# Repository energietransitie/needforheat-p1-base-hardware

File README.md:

# NeedForHeat P1-BASE hardware <!-- omit in toc -->

This repository contains the open hardware design files for the NeedForHeat P1-BASE device, which can be used as a [CoreInk BASE extension module](https://docs.m5stack.com/en/coreink/proto_base), on the back of an [M5Stack CoreInk](https://docs.m5stack.com/en/core/coreink) device. 

The NeedForHeat P1-BASE enables reading [smart meters that adhere to the Dutch Smart Meter Requirements](https://github.com/energietransitie/dsmr-info) via the [P1 port](https://nl.wikipedia.org/wiki/P1-poort).

## Table of contents <!-- omit in toc -->
- [General info](#general-info)
- [Producing](#producing)
  - [Printed Circuit Board](#printed-circuit-board)
  - [Enclosure](#enclosure)
- [Deploying](#deploying)
  - [Cost](#cost)
  - [Connecting](#connecting)
  - [Setting the DIP Switches](#setting-the-dip-switches)
- [Developing](#developing)
  - [Printed Circuit Board](#printed-circuit-board-1)
- [Features](#features)
- [Status](#status)
- [License](#license)
- [Credits](#credits)

## General info
This repository contains the open hardware designs files for the NeedForHeat P1-BASE. It also includes a `docs` folder with recent printouts of the [schematics](./docs/needforheat-p1-base-hardware-sch.pdf) and [PCB layout](./docs/needforheat-p1-base-hardware-pcb.pdf). 

For the associated firmware that you can run on this device, please see [this repository](https://github.com/energietransitie/needforheat-p1-reader-firmware).

## Producing

### Printed Circuit Board
To manufacture the printed circuit board you can use various PCB services. 

The folder [pcb/jlcpcb](./pcb/jlcpcb) includes all exported files needed to have the PCBs manufactured by [JLCPCB](https://www.jlcpcb.com). Upload the [zipped gerber files](./pcb/jlcpcb/assembly/GERBER-needforheat-p1-base-hardware.zip) to the [JLCPCB quote page](https://cart.jlcpcb.com/quote), select the amount of PCBs and a colour for the silkscreen. All other options can be left on default. 

If you do not want to solder components on the PCB yourself, select `PCB assembly` and JLCPCB will do it for you (even for through-hole components if you so desire). This will take you to a page where the BOM and POS file can be uploaded. Use the files [BOM-needforheat-p1-base-hardware.csv](./pcb/jlcpcb/assembly/BOM-needforheat-p1-base-hardware.csv) and [CPL-needforheat-p1-base-hardware.csv](./pcb/jlcpcb/assembly/CPL-needforheat-p1-base-hardware.csv).

JLCPCB provides detailed steps on their website to select component assembly, including wave soldering. For wave soldering or through-hole component assembly, specify this requirement when uploading your BOM and POS files. 

> After uploading BOM and CPL, you may be asked to select a component for `Q3`. You do not need to do so and can select 'do not place'. For more information, see the [design document](docs/documentation.md#optional-components).

### Enclosure

An enclosure for this device has not been developed yet.

<!-- an enclosure has not been developed yet
To fabricate the enclosure you can use your own 3D printer or use a 3D printing service. 

The folder [enclosure/fabrication](./enclosure/fabrication) contains exported STL files for the [case](./enclosure/fabrication/twomes-hardware-repository-template-case.stl) and [lid](./enclosure/twomes-hardware-repository-template-lid.step) of the NeedForHeat P1-BASE enclosure. The STL files can be imported into any slicer and turned into G-Code for a 3D printer.
-->

## Deploying

To deploy P1-BASE to a home as the NeedForHeat Smart Meter module, in addition to the PCB you need additional hardware: enclusure, M5Stack CoreInk, a short RJ12 cable and for some homes a power adapter. In this section we describe the cose and connections.

### Cost

Prices indicate price per module in June 2024, based on ordering enough hardware for 10 modules, including 21% VAT and shipping to an address in the Netherlands.

| #   | Item                                                                                                                                                 | Supplier    | Price per Unit |   Subtotal |  Shipping |      Total |
| --- | ---------------------------------------------------------------------------------------------------------------------------------------------------- | ----------- | -------------: | ---------: | --------: | ---------: |
| 1   | P1-BASE PCB                                                                                                                                          | JLCPCB      |          €2.40 |      €2.40 |     €2.38 |      €4.78 |
| 1   | P1-BASE enclosure                                                                                                                                    | JLCPCB      |          €1,30 |      €1,30 |     €2,40 |      €3,60 |
| 1   | [M5Stack CoreInk](https://www.tinytronics.nl/nl/platformen-en-systemen/m5stack/e-paper/m5stack-m5core-ink-met-1.54-inch-e-paper-e-ink-display-esp32) | TinyTronics |         €43.00 |     €43.00 |     €0.00 |     €43.00 |
| 4   | [LEGO pen stroef + pen stroef](https://www.blokjeskoning.nl/product/pen-stroef-pen-stroef-zwart/) | Blokjeskoning |         €0.03 |   €0.12 |    €0.30 | €0.42 |
| 1   | [RJ12 cable (male-male; 6P6C; straight; 0.5 m or shorter)](https://www.amazon.nl/-/en/InLine-18848A-Modular-Cable-6-Core/dp/B005I1UDOE/)[^1]         | AlleKabels  |          €5.95 |      €5.95 |     €0.00 |      €5.95 |
| 1   | [USB-A 230V charger + USB-A to USB-C cable](https://www.allekabels.nl/usb-oplader/4508/3636716/usb-a-oplader-usb-c-kabel.html)                       | AlleKabels  |         €14.95 |     €14.95 |     €0.13 |     €15.08 |
|     | **TOTAL**                                                                                                                                            |             |     **€67.60** | **€67.72** | **€6,21** | **€72,83** |

[^1]: The shorter the cable the better: this allows users to simply click in the RJ12 connector of te to the P1 port of their smart to leave and leave the NeedForHeat smart meter reader device dangling from the P1-port;*

### Connecting

Assuming that the PCB is fully assembled, the device has an enclosure, and the device has been programmed with the [needforheat-p1-reader-firmware](https://github.com/energietransitie/needforheat-p1-reader-firmware), you can proceed and connect the device as follows:

Before sending the device to a home:

1. Mount the P1-BASE in its enclosure.
1. Connect the short RJ12 cable to the upper female RJ12 connector[^2].
1. Insert 2 lego pens in the enclusure at opposite diagonal corners. 
1. Insert 2 lego pens in the holes on the back side of the M5Stack CoreInk at opposite diagonal corners.
4. Do NOT connect the P1_BASE and M5Stack CoreInk, before sending, since they will not fit in a standard [PostNL brievenbusdoos](https://shop.postnl.nl/webshop/verpakkingen/brievenbusdoos-a5-255x160x28mm) when stacked.

[^2]: By pre-connecting the RJ12 cable to connector `J2` on the PCB, you help users at home avoid installation errors. You may even consider clipping off 3 to 4 mm from the latch of the modular conector. After insertion the connector does not protrude from the female connecto, which clearly signals to the user that this cable should not be deinstalled. 

After receiving the device in a home:
1. Connect to the P1-BASE to the based of the M5Stack CoreInk, ensuring alignment of M5Stack CoreInk with the P1-BASE; the LEGO pins will help make sure that the 2x8 pin connector of the P1-BASE properly connects to M5Stack CoreInk.
2. Unplug your existing smart meter reader (if any) from the P1 port smart meter
3. Connect the plug of the NeedForHeat smart meter module in the P1 port .
4. Plug the RJ16 connector of our existing smart meter reader into the bottom RJ12 socket of the P1-BASE.

### Setting the DIP Switches

The hardware version v2.7 (2024-06-07) features 3 DIP switches on the PCB to control data request line management. Adjust the switches according to the following settings before delivering the device to the user:

| DIP-switch Number | ON Position                                        | OFF Position                                          |
| ----------------- | -------------------------------------------------- | ----------------------------------------------------- |
| 1                 | Data requested continuously (DSMR 4 & 5)           | Data not requested continuously                       |
| 2                 | Data request driven by M5Stack CoreInk             | Data request from M5Stack CoreInk ignored             |
| 3                 | Data request driven by external smart meter reader | Data request from external smart meter reader ignored |

If multiple DIP switches are ON simultaneously, data is requested if any corresponding source requires it. This may cause the external smart meter reader to receive partial messages, but according to the [DSMR P1 Port Companion Standard](https://github.com/energietransitie/dsmr-info?tab=readme-ov-file#dsmr-versions-standards) since version 3.0, smart meter readers should be able to handle partial messages.

## Developing

### Printed Circuit Board
To change the hardware design of the PCB, you need:
* [KiCad version 8.0.0 or later](https://www.kicad.org/download/) installed to change te PCB design. 

The KiCad source files of the PCB can be found in the folder [pcb](./pcb).

To convert the PCBs into a format suitable for fabrication, consult the webpage of your PCB manufacturer of choice. For example, see the [JLCPCB guide on how to export Gerbers](https://support.jlcpcb.com/article/149-how-to-generate-gerber-and-drill-files-in-kicad) and the  [JLCPCB guide how to export the BOM and POS files](https://support.jlcpcb.com/article/84-how-to-generate-the-bom-and-centroid-file-from-kicad). You may also use a KiCad plug-in for this purpose such as [kicad-jlcpcb-tools](https://github.com/Bouni/kicad-jlcpcb-tools).

<!-- 
### Enclosure
To change the hardware design of the enclosure, you need either:
* [Autodesk Fusion 360](https://www.kicad.org/download/) installed (Autodesk provides 30 day free trials and [free one-year educational access](https://www.autodesk.com/education/edu-software/overview?sorting=featured&filters=individual) to its products and services for eligible students, teachers and research staff); 
* or [FreeCAD](https://www.freecadweb.org/), an open source alternative.

The source files of the enclosure can be found in the folder [enclosure](./enclosure). We include both .f3d source files and .step source files we obtained after conversion.
-->

## Features

The NeedForHeat P1-BASE includes the following main hardware components:

- [x] Built-in P1-splitter for connecting an additional smart meter reader to the lower female RJ12 connector (`J3`).
- [x] Integrated [Schmitt trigger](https://en.wikipedia.org/wiki/Schmitt_trigger) to reduce signal noise.
- [x] 3 DIP-switches on the PCB for enabling/disabling data request line management.
- [x] Bottom-side 2x8 pin header for MI-BUS connection to the [M5Stack CoreInk](https://docs.m5stack.com/en/core/coreink) (requires soldering yourself, or a hefty JLCPCB fee for bottom-side hand-soldering).

To-do:

- [ ] Test compatibility with Landis+Gyr E360 series smart meters (e.g., [Landis+Gyr CD2D](https://www.landisgyr.eu/), [CM3D](https://www.landisgyr.eu/)).
- [ ] Consider using 'upside-down' RJ12 female connectors for easier [M5Stack CoreInk](https://docs.m5stack.com/en/core/coreink) screen readability.
- [ ] Evaluate relocating and optimizing the 2x8 pin header from the bottom side to the top side of the PCB to reduce manufacturing costs. 
  > (This would also obviate the need for 'upside-down' RJ12 female connectors, above.)
- [ ] Refine PCB design to reduce clutter where possible.
- [ ] Experiment with alternative data request management methods (e.g., MOSFETs, BJTs), which would allow the [M5Stack CoreInk](https://docs.m5stack.com/en/core/coreink) to check and control data request management in software.
- [ ] Implement low-power LEDs for indicating power status, data request status, and data flow.
- [ ] Develop energy-efficient charging strategies for the [M5Stack CoreInk](https://docs.m5stack.com/en/core/coreink) 390 mAh LiPo battery from DSMR 4 and DSMR 5 smart meters, without triggering the fold-back current limiting feature of some smart meters.
- [ ] Design a 3D-printable enclosure compatible with the [M5Stack CoreInk](https://docs.m5stack.com/en/core/coreink), potentially using [LEGO connector pens](https://www.blokjeskoning.nl/product/pen-stroef-pen-stroef-zwart/). A preliminary version can be found in the [needforheat-boiler-monitor-hardware repository](https://github.com/energietransitie/needforheat-boiler-monitor-hardware).

## Status
Project is:  _in progress_

## License
The hardware designs in this repository are available under the [CERN-OHL-P v2 license](./LICENSE), Copyright 2024 [Research group Energy Transition, Windesheim University of Applied Sciences](https://windesheim.nl/energietransitie)

## Credits
This open hardware design is a collaborative effort of:
* Rick de Graaf · [@277r](https://github.com/277r) 
* Gerwin ten Have · [@GerwintenHave](https://github.com/GerwintenHave) 

Product owners:
* Henri ter Hofte · [@henriterhofte](https://github.com/henriterhofte) · Twitter [@HeNRGi](https://twitter.com/HeNRGi)
* Marco Winkelman · [@MarcoW71](https://github.com/MarcoW71)

We use and gratefully acknowlegde the efforts of the makers of:
* [Twomes P1 Gateway Hardware](https://github.com/energietransitie/twomes-p1-gateway-hardware), by Research group Energy Transition at Windesheim University of Applied Sciences, licenced under Apache 2.0
* [KiCad Libraries](https://kicad.github.io/), by the KiCad Development Team, licensed under [an adapted version of the CC-BY-SA 4.0 License](https://www.kicad.org/libraries/license/)

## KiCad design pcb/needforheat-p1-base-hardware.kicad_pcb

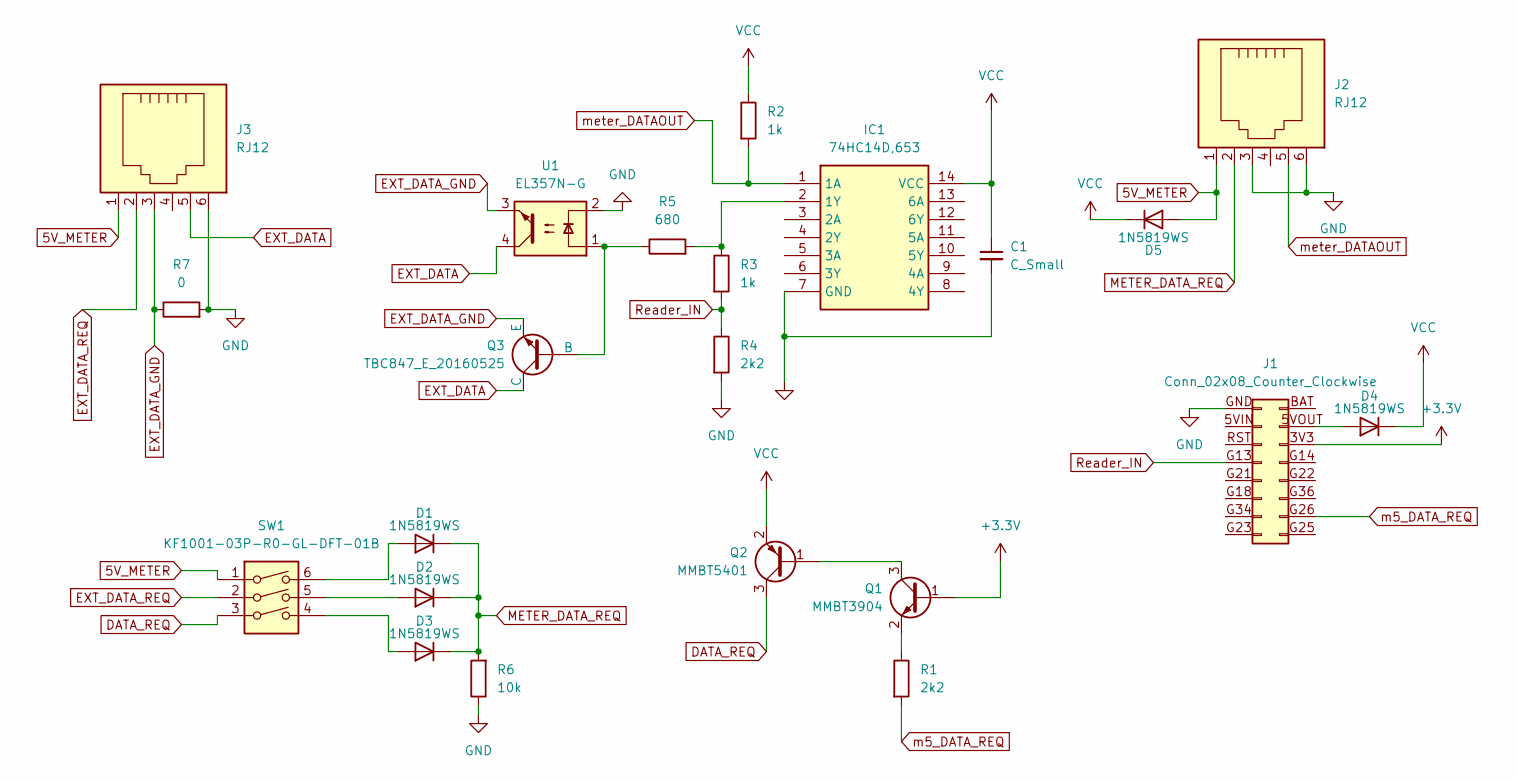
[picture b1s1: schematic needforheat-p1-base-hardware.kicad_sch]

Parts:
C1: C_Small; C_0805_2012Metric
D1, D2, D3, D4, D5: 1N5819WS; D_SOD-323
IC1: 74HC14D,653; SOIC127P600X175-14N; Mouser Part Number 771-74HC14D-T
J1: Conn_02x08_Counter_Clockwise; PinHeader_2x08_P2.54mm_Vertical
J2, J3: RJ12; RJ25_Wayconn_MJEA-660X1_Horizontal
Q1: MMBT3904; SOT-23
Q2: MMBT5401; SOT-23
Q3: TBC847_E_20160525; SOT-23-3
R1, R4: 2k2; R_0805_2012Metric
R2, R3: 1k; R_0805_2012Metric
R5: 680; R_0805_2012Metric
R6: 10k; R_0805_2012Metric
R7: 0; R_0805_2012Metric
SW1: KF1001-03P-R0-GL-DFT-01B; DIP-6_W7.62mm_Socket
U1: EL357N-G; SOP-4_3.8x4.1mm_P2.54mm

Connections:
5V_METER: D5.2 (A), J2.1, J3.1, SW1.1
+3.3V: J1.3V3 (Pin_14), Q1.1 (B)
DATA_REQ: Q2.3 (C), SW1.3
EXT_DATA: J3.5, Q3.1 (C), U1.4
EXT_DATA_GND: J3.3, Q3.3 (E), R7.1, U1.3
EXT_DATA_REQ: J3.2, SW1.2
GND: C1.2, IC1.7 (GND), J1.GND (Pin_1), J2.3, J2.6, J3.6, R4.2, R6.1, R7.2, U1.2
METER_DATA_REQ: D1.1 (K), D2.1 (K), D3.1 (K), J2.2, R6.2
unnamed: D1.2 (A), SW1.6
unnamed: D2.2 (A), SW1.5
unnamed: D3.2 (A), SW1.4
unnamed: D4.2 (A), J1.5VOUT (Pin_15)
unnamed: IC1.2 (1Y), R3.1, R5.2
unnamed: Q1.3 (C), Q2.1 (B)
unnamed: Q1.2 (E), R1.1
unnamed: Q3.2 (B), R5.1, U1.1
Reader_IN: J1.G13 (Pin_4), R3.2, R4.1
VCC: C1.1, D4.1 (K), D5.1 (K), IC1.14 (VCC), Q2.2 (E), R2.1
m5_DATA_REQ: J1.G26 (Pin_10), R1.2
meter_DATAOUT: IC1.1 (1A), J2.5, R2.2

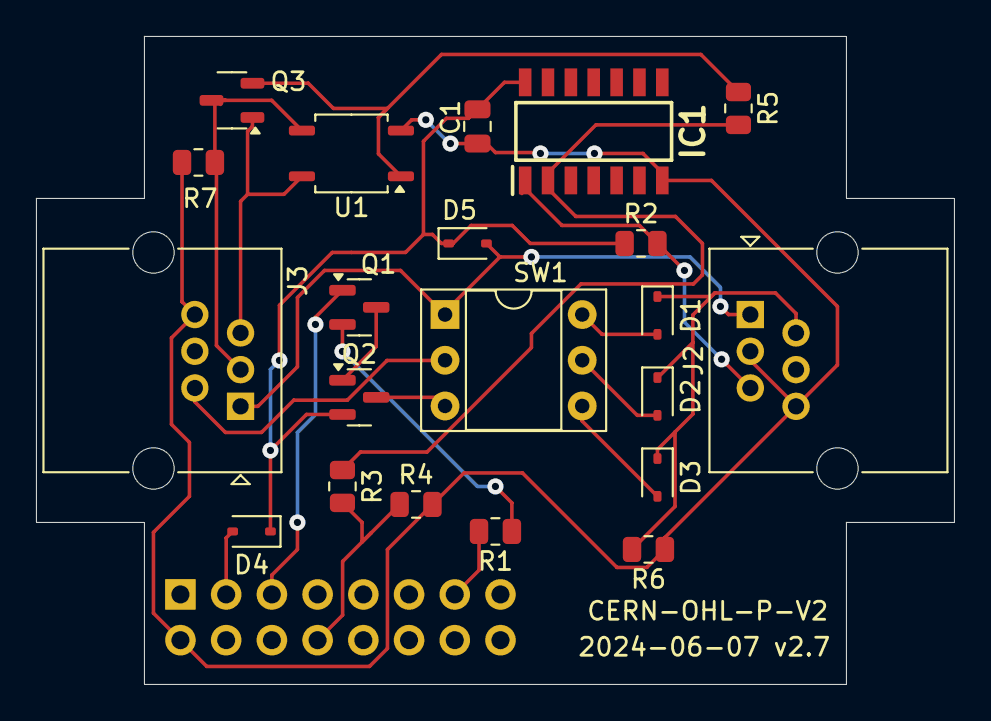
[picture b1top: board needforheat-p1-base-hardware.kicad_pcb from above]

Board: 2 copper layers, 51.0 x 36.0 mm, 22 parts (1 on the bottom side), 20 nets.

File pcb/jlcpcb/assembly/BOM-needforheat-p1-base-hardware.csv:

Comment,Designator,Footprint,LCSC
10k,R6,R_0805_2012Metric,C17414
1k,"R2,R3",R_0805_2012Metric,C17513
2k2,"R1,R4",R_0805_2012Metric,C17520
1N5819WS,"D1,D2,D3,D4,D5",D_SOD-323,C191023
MMBT3904,Q1,SOT-23,C20526
680,R5,R_0805_2012Metric,C23228
EL357N-G,U1,SOP-4_3.8x4.1mm_P2.54mm,C29981
C_Small,C1,C_0805_2012Metric,C49678
"74HC14D,653",IC1,SOIC127P600X175-14N,C5605
Conn_02x08_Counter_Clockwise,J1,PinHeader_2x08_P2.54mm_Vertical,C68234
RJ12,"J2,J3",RJ25_Wayconn_MJEA-660X1_Horizontal,C77859
MMBT5401,Q2,SOT-23,C8326
KF1001-03P-R0-GL-DFT-01B,SW1,DIP-6_W7.62mm_Socket,C976325
TBC847_E_20160525,Q3,SOT-23-3,

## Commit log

2024-05-29 Added KiCAD Project and JLCPCB production files
2024-05-30 update generic names to NeedForHeat P1-BASE
2024-06-10 updated the pcb files to p1-base v2.4
2024-06-10 added images
2024-06-10 added documentation, added people to credits after receiving permission to do so, added schematic
2024-06-12 spliiter information added
2024-06-13 splitter picture added
2024-06-13 splitter information adjusted
    I changed to information for the splitter to make it more logical and to explain the image I put in earlier
2024-06-13 splitter looked messy
    added enters to make the splitter information more readable
2024-06-18 added pcb, schematic
2024-06-20 updated images
2024-06-24 improved deployment manual, clarified descriptions, improved readability
2024-06-24 acknowledge KiCad Libraries
2024-06-24 fixed relative link error
2024-06-24 fixed another relatve link error
2024-06-24 omit upper headers in toc
2024-06-24 fix typos
2024-06-26 reorganized jlcpcb file locations and added cost estimate
